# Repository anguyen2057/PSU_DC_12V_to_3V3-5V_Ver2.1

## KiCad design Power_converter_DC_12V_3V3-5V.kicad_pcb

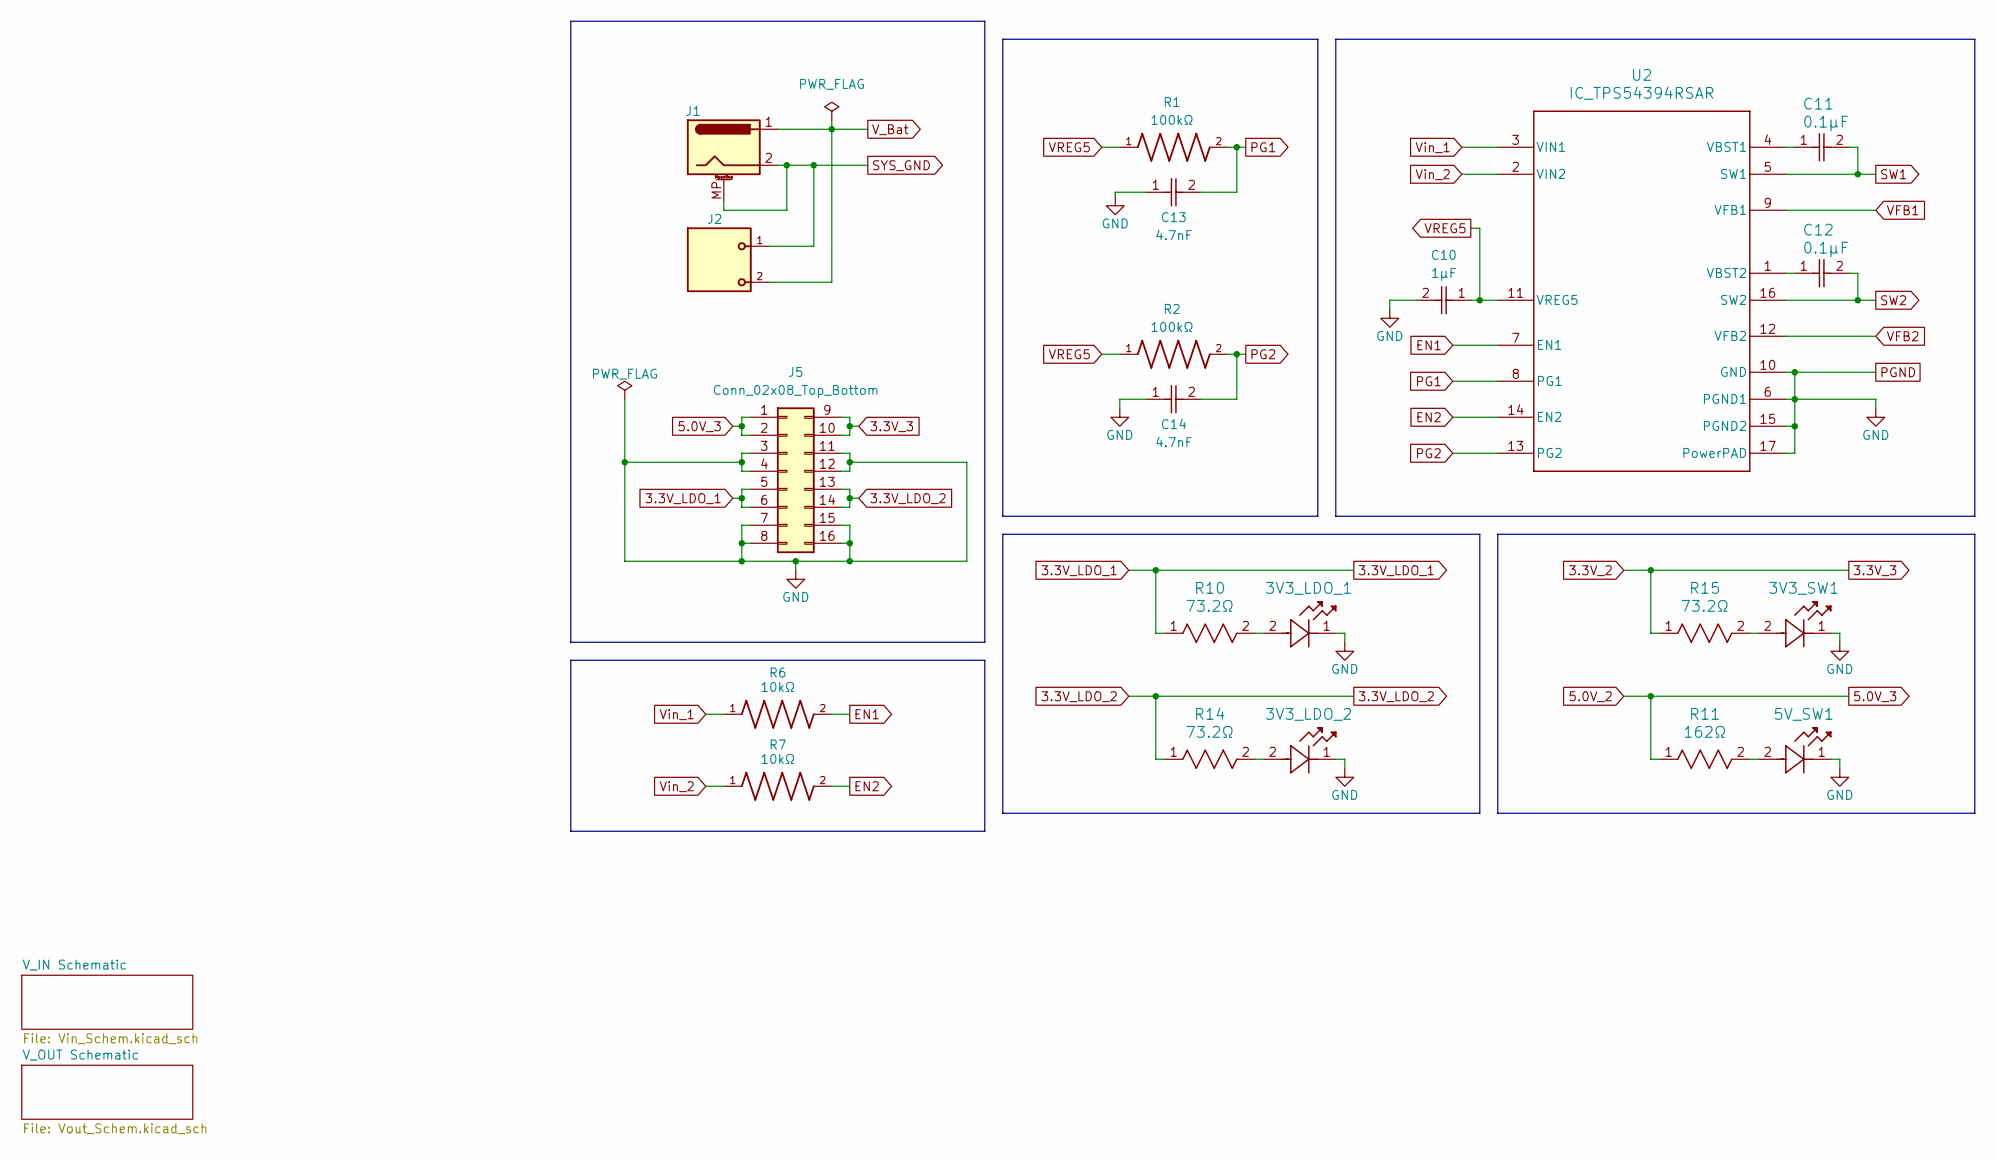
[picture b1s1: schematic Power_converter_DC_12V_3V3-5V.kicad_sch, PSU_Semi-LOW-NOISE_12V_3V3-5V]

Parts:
3V3_LDO_1, 3V3_LDO_2, 3V3_SW1, 5V_SW1: LED_1.9V_Forward_SML-E12DWT86; LED_SMLD12_ROM
C10: 1µF; CAPC1608X90N; DigiKey_Part_Number 445-5146-2-ND
C11, C12: 0.1µF; CAP_CL10_SAM
C13, C14: 4.7nF; CAPC1608X90
J1: Barrel_Jack_MountingPin; BarrelJack_Wuerth_6941xx301002
J2: 691412120002B; PART-NUMBER 691412120002B
J5: Conn_02x08_Top_Bottom; PinHeader_2x08_P2.54mm_Vertical
R1, R2: 100kΩ; RES_ERJP06D1003V; PARTREV 3/1/2020
R6, R7: 10kΩ; RESC3015X65N
R10, R14, R15: 73.2Ω; RC1206N_YAG
R11: 162Ω; RC1206N_YAG
U2: IC_TPS54394RSAR; RSA0016B-IPC_A

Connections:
3.3V_2: J5.9, J5.10, R15.1; also elsewhere on the board
3.3V_LDO_1: J5.5, J5.6, R10.1; also elsewhere on the board
3.3V_LDO_2: J5.13, J5.14, R14.1; also elsewhere on the board
5.0V_2: J5.1, J5.2, R11.1; also elsewhere on the board
EN1: R6.2, U2.7 (EN1)
EN2: R7.2, U2.14 (EN2)
unnamed: 3V3_LDO_1.2, R10.2
unnamed: 3V3_LDO_2.2, R14.2
unnamed: 3V3_SW1.2, R15.2
unnamed: 5V_SW1.2, R11.2
unnamed: C11.1, U2.4 (VBST1)
unnamed: C12.1, U2.1 (VBST2)
PG1: C13.2, R1.2, U2.8 (PG1)
PG2: C14.2, R2.2, U2.13 (PG2)
PGND: 3V3_LDO_1.1, 3V3_LDO_2.1, 3V3_SW1.1, 5V_SW1.1, C10.2, C13.1, C14.1, J5.3, J5.4, J5.7, J5.8, J5.11, J5.12, J5.15, J5.16, U2.6 (PGND1), U2.10 (GND), U2.15 (PGND2), U2.17 (PowerPAD); also elsewhere on the board
SW1: C11.2, U2.5 (SW1); also elsewhere on the board
SW2: C12.2, U2.16 (SW2); also elsewhere on the board
SYS_GND: J1.2, J1.3, J1.MP (MountPin), J2.1; also elsewhere on the board
VFB1: U2.9 (VFB1); also elsewhere on the board
VFB2: U2.12 (VFB2); also elsewhere on the board
VREG5: C10.1, R1.1, R2.1, U2.11 (VREG5)
V_Bat: J1.1, J2.2; also elsewhere on the board
Vin_1: R6.1, U2.3 (VIN1); also elsewhere on the board
Vin_2: R7.1, U2.2 (VIN2); also elsewhere on the board

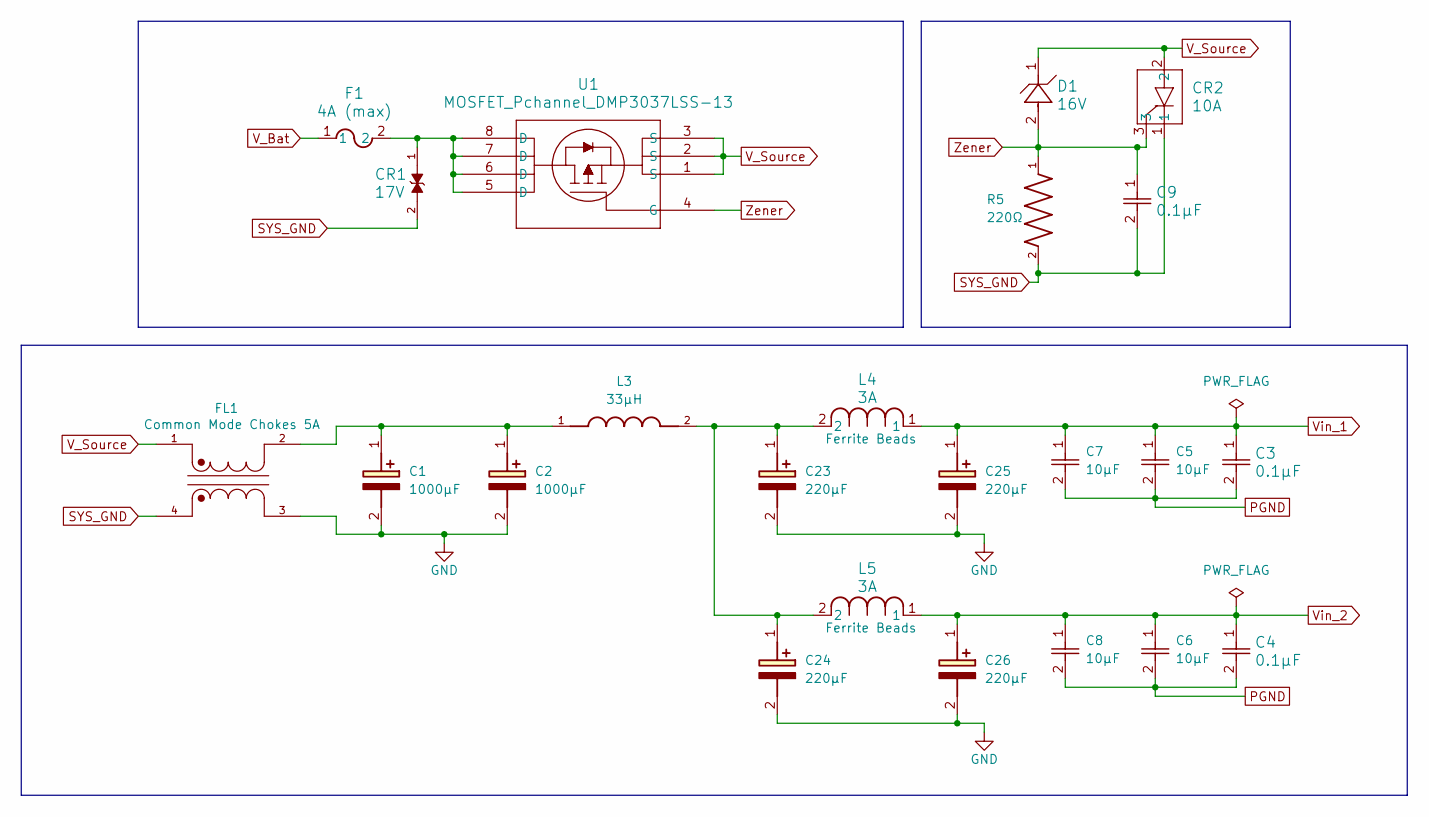
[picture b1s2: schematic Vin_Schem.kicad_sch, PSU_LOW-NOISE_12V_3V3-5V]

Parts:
C1, C2: 1000µF; CAPPRD500W65D1000H1600; Mouser Part Number 80-A750MV108M1EAAE14
C3, C4, C9: 0.1µF; CAP_CL10_SAM
C5, C6, C7, C8: 10µF; CAPC3216X140N
C23, C24, C25, C26: 220µF; CAPPRD350W65D800H1300; Mouser Part Number A750KS227M1EEAE015
CR1: 17V; SMASeries_LTF
CR2: 10A; DPAK_6p73x6p22-2p286_STM
D1: 16V; SOD323F_DIO
F1: 4A (max); FUSE_31.8221_SCH
FL1: Common Mode Chokes 5A; FIL_ACMP-5025-251-T; PARTREV B
L3: 33µH; IND_ETQP4M330KVC; PARTREV 1-Feb-20
L4, L5: 3A; IND_1608_TDK
R5: 220Ω; RESC3116X65N
U1: MOSFET_Pchannel_DMP3037LSS-13; SO8_DIO

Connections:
unnamed: C1.1 (+), C2.1 (+), FL1.2, L3.1
unnamed: C23.1 (+), C24.1 (+), L3.2, L4.2, L5.2
unnamed: CR1.1, F1.2, U1.5 (D), U1.6 (D), U1.7 (D), U1.8 (D)
PGND: C1.2 (-), C2.2 (-), C3.2, C4.2, C5.2, C6.2, C7.2, C8.2, C23.2 (-), C24.2 (-), C25.2 (-), C26.2 (-), FL1.3; also elsewhere on the board
SYS_GND: C9.2, CR1.2, CR2.1, FL1.4, R5.2; also elsewhere on the board
V_Bat: F1.1; also elsewhere on the board
V_Source: CR2.2, D1.1, FL1.1, U1.1 (S), U1.2 (S), U1.3 (S)
Vin_1: C3.1, C5.1, C7.1, C25.1 (+), L4.1; also elsewhere on the board
Vin_2: C4.1, C6.1, C8.1, C26.1 (+), L5.1; also elsewhere on the board
Zener: C9.1, CR2.3, D1.2, R5.1, U1.4 (G)

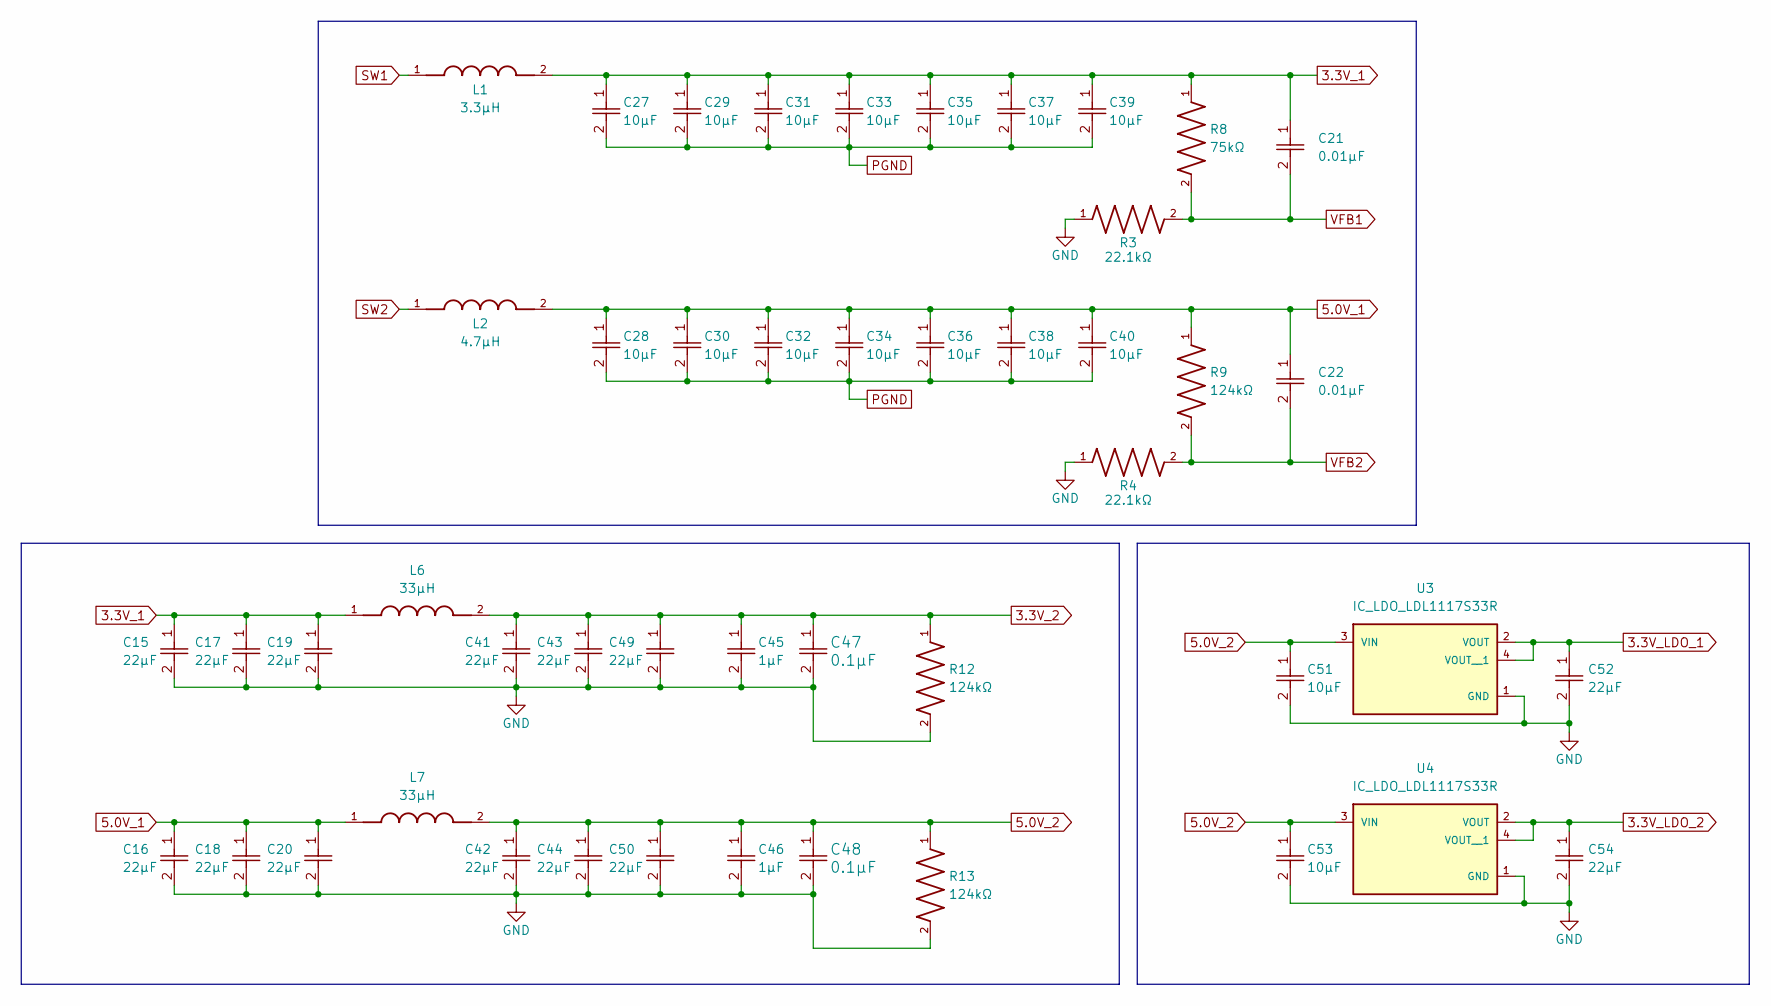
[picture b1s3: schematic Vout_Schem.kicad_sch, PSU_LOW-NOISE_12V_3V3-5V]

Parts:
C15, C16, C17, C18, C19, C20, C41, C42, C43, C44, C49, C50, C52, C54: 22µF; CAPC3216X180N
C21, C22: 0.01µF; CAPC1608X90N
C27, C28, C29, C30, C31, C32, C33, C34, C35, C36, C37, C38, C39, C40, C51, C53: 10µF; CAPC3216X140N
C45, C46: 1µF; CAPC1608X90N; DigiKey_Part_Number 445-5146-2-ND
C47, C48: 0.1µF; CAP_CL10_SAM
L1: 3.3µH; IND_VLS6045EX-3R3N; PARTREV N/A
L2: 4.7µH; IND_VLS6045EX-4R7M; PARTREV N/A
L6, L7: 33µH; IND_ETQP4M330KFM; PARTREV 1-Feb-20
R3, R4: 22.1kΩ; RESC2012X60N
R8: 75kΩ; RESC2012X60N
R9, R12, R13: 124kΩ; RES_ERJ-PB6B1243V; PARTREV 3/1/2020
U3, U4: IC_LDO_LDL1117S33R; SOT230P700X180-4N; PARTREV 7

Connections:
3.3V_1: C15.1, C17.1, C19.1, C21.1, C27.1, C29.1, C31.1, C33.1, C35.1, C37.1, C39.1, L1.2, L6.1, R8.1
3.3V_2: C41.1, C43.1, C45.1, C47.1, C49.1, L6.2, R12.1; also elsewhere on the board
3.3V_LDO_1: C52.1, U3.2 (VOUT), U3.4 (VOUT__1); also elsewhere on the board
3.3V_LDO_2: C54.1, U4.2 (VOUT), U4.4 (VOUT__1); also elsewhere on the board
5.0V_1: C16.1, C18.1, C20.1, C22.1, C28.1, C30.1, C32.1, C34.1, C36.1, C38.1, C40.1, L2.2, L7.1, R9.1
5.0V_2: C42.1, C44.1, C46.1, C48.1, C50.1, C51.1, C53.1, L7.2, R13.1, U3.3 (VIN), U4.3 (VIN); also elsewhere on the board
PGND: C15.2, C16.2, C17.2, C18.2, C19.2, C20.2, C27.2, C28.2, C29.2, C30.2, C31.2, C32.2, C33.2, C34.2, C35.2, C36.2, C37.2, C38.2, C39.2, C40.2, C41.2, C42.2, C43.2, C44.2, C45.2, C46.2, C47.2, C48.2, C49.2, C50.2, C51.2, C52.2, C53.2, C54.2, R3.1, R4.1, R12.2, R13.2, U3.1 (GND), U4.1 (GND); also elsewhere on the board
SW1: L1.1; also elsewhere on the board
SW2: L2.1; also elsewhere on the board
VFB1: C21.2, R3.2, R8.2; also elsewhere on the board
VFB2: C22.2, R4.2, R9.2; also elsewhere on the board

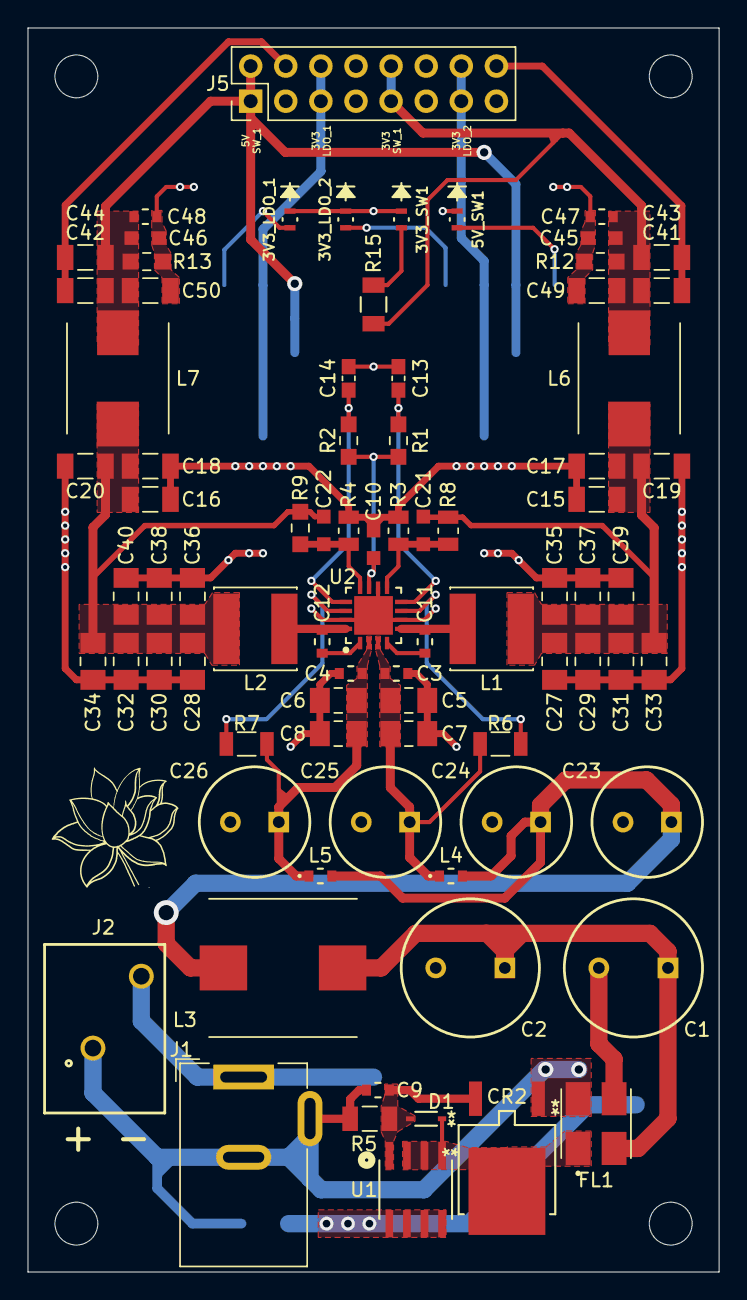
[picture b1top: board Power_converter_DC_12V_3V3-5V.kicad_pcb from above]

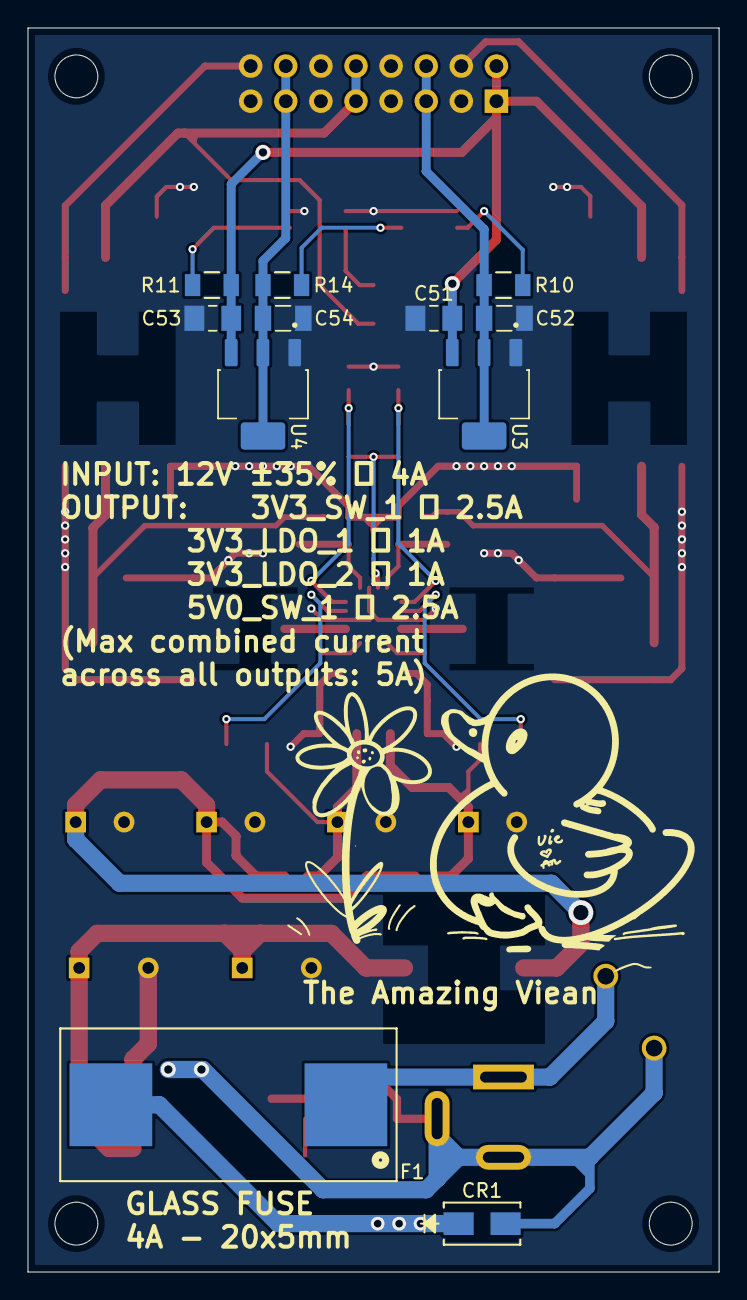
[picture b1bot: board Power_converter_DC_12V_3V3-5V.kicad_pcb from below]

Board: 2 copper layers, 50.0 x 90.0 mm, 93 parts (12 on the bottom side), 31 nets.

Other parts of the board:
The Amazing Viean: LOGO; Logo_Drawing

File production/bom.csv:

Designator,Footprint,Quantity,Value,LCSC Part #
"3V3_LDO_1, 3V3_LDO_2, 3V3_SW1, 5V_SW1",LED_SMLD12_ROM,4,LED_1.9V_Forward_SML-E12DWT86,
"C1, C2",CAPPRD500W65D1000H1600,2,1000µF,
"C10, C45, C46",CAPC1608X90N,3,1µF,
"C11, C12, C3, C4, C47, C48, C9",CAP_CL10_SAM,7,0.1µF,
"C13, C14",CAPC1608X90,2,4.7nF,
"C15, C16, C17, C18, C19, C20, C41, C42, C43, C44, C49, C50, C52, C54",CAPC3216X180N,14,22µF,
"C21, C22",CAPC1608X90N,2,0.01µF,
"C23, C24, C25, C26",CAPPRD350W65D800H1300,4,220µF,
"C27, C28, C29, C30, C31, C32, C33, C34, C35, C36, C37, C38, C39, C40, C5, C51, C53, C6, C7, C8",CAPC3216X140N,20,10µF,
CR1,SMASeries_LTF,1,17V,
CR2,DPAK_6p73x6p22-2p286_STM,1,10A,
D1,SOD323F_DIO,1,16V,
F1,FUSE_31.8221_SCH,1,4A (max),
FL1,FIL_ACMP-5025-251-T,1,Common Mode Chokes 5A,
J1,BarrelJack_Wuerth_6941xx301002,1,Barrel_Jack_MountingPin,
J2,691412120002B,1,691412120002B,
J5,PinHeader_2x08_P2.54mm_Vertical,1,Conn_02x08_Top_Bottom,
L1,IND_VLS6045EX-3R3N,1,3.3µH,
L2,IND_VLS6045EX-4R7M,1,4.7µH,
L3,IND_ETQP4M330KVC,1,33µH,
"L4, L5",IND_1608_TDK,2,3A,
"L6, L7",IND_ETQP4M330KFM,2,33µH,
"R1, R2",RES_ERJP06D1003V,2,100kΩ,
"R10, R14, R15",RC1206N_YAG,3,73.2Ω,
R11,RC1206N_YAG,1,162Ω,
"R12, R13, R9",RES_ERJ-PB6B1243V,3,124kΩ,
"R3, R4",RESC2012X60N,2,22.1kΩ,
R5,RESC3116X65N,1,220Ω,
"R6, R7",RESC3015X65N,2,10kΩ,
R8,RESC2012X60N,1,75kΩ,
U1,SO8_DIO,1,MOSFET_Pchannel_DMP3037LSS-13,
U2,RSA0016B-IPC_A,1,IC_TPS54394RSAR,
"U3, U4",SOT230P700X180-4N,2,IC_LDO_LDL1117S33R,

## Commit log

2025-05-24 Self-Made Footprints and Other
2025-05-24 Kicad library
2025-05-24 Production file
